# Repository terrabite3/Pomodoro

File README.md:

# Pomodoro

This is a tomato-shaped timer that counts down from 25 minutes.

## Hardware

* ATmega328p or compatible (I used ATmega8 due to supply chain issues)
* USB Micro-B power
* Four-digit 7-segment multiplexed display with colon LEDs
* Reset button
* Wheel potentiometer to adjust brightness
* Extra GPIO is exposed on a header
* Designed to be mostly assembled by JLCPCB

## Software

* Hard-coded 25 minute countdown
* Flashes 00:00 for one minute after countdown finishes
* Full shutdown after count is complete to save power
* Brightness adjustment goes down "off" to reduce visual distraction. At the start of the countdown, the display will start on and fade down to the selected brightness after 10 seconds. The flashing at the end of the countdown ignores the brightness setting.

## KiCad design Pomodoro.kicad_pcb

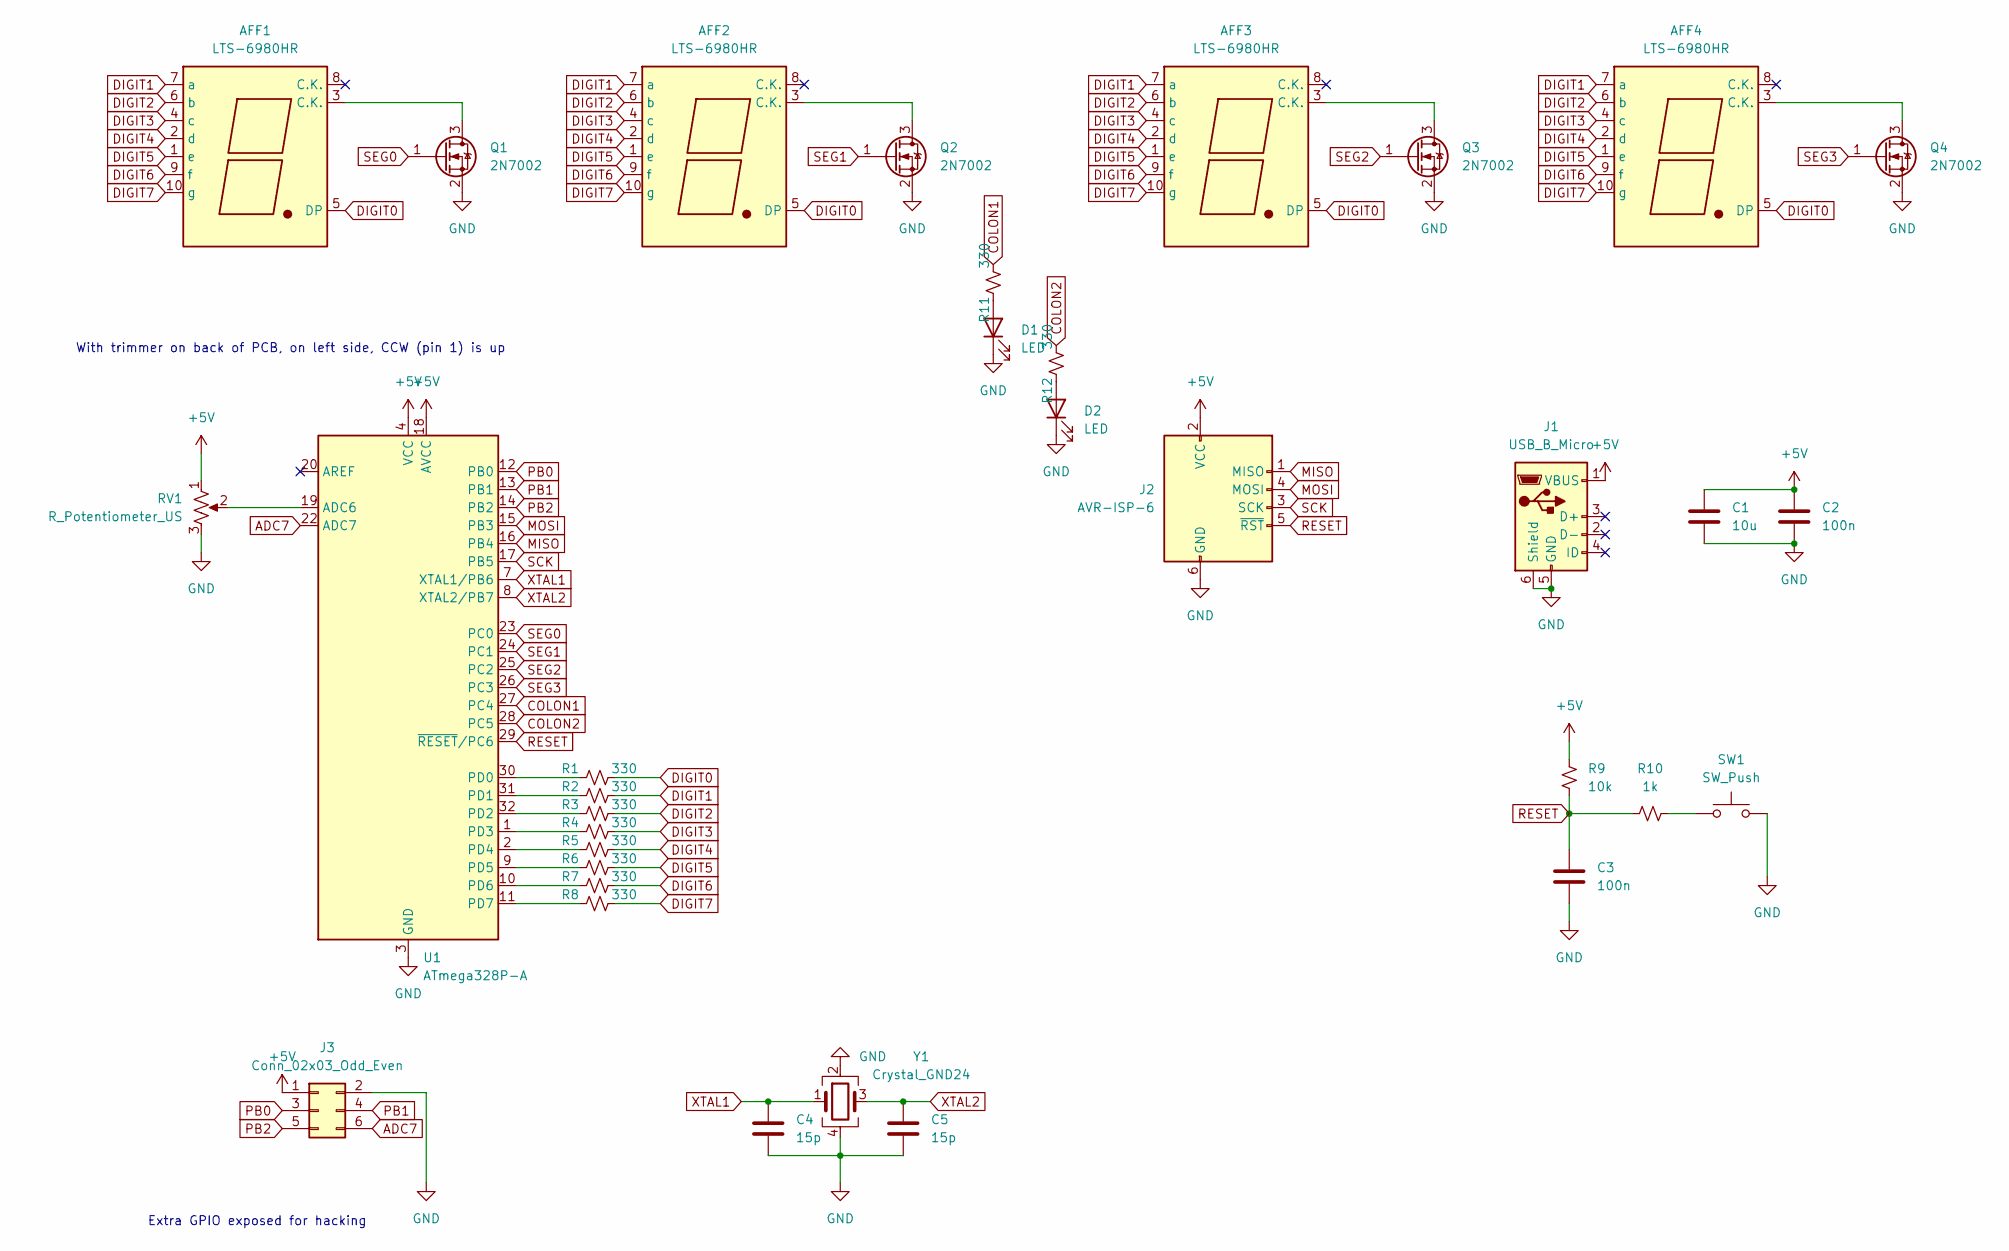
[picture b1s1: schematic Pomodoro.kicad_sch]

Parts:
AFF1, AFF2, AFF3, AFF4: LTS-6980HR; 7SegmentLED_LTS6760_LTS6780
C1: 10u; C_0805_2012Metric
C2, C3: 100n; C_0402_1005Metric
C4, C5: 15p; C_0402_1005Metric
D1, D2: LED; LED_D3.0mm
J1: USB_B_Micro; USB_Micro-B_Amphenol_10118194_Horizontal
J2: AVR-ISP-6; PinHeader_2x03_P2.54mm_Vertical_SMD
J3: Conn_02x03_Odd_Even; PinHeader_2x03_P2.54mm_Vertical_SMD
Q1, Q2, Q3, Q4: 2N7002; SOT-23
R1, R2, R3, R4, R5, R6, R7, R8, R11, R12: 330; R_0402_1005Metric
R9: 10k; R_0402_1005Metric
R10: 1k; R_0402_1005Metric
RV1: R_Potentiometer_US; Potentiometer_Bourns_3352T
SW1: SW_Push; SW_PUSH_6mm
U1: ATmega328P-A; TQFP-32_7x7mm_P0.8mm
Y1: Crystal_GND24; Crystal_SMD_3225-4Pin_3.2x2.5mm

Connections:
+5V: C1.1, C2.1, J1.1 (VBUS), J2.2 (VCC), J3.1, R9.2, RV1.1, U1.4 (VCC), U1.6 (VCC), U1.18 (AVCC)
ADC7: J3.6, U1.22 (ADC7)
COLON1: R11.2, U1.27 (PC4)
COLON2: R12.2, U1.28 (PC5)
DIGIT0: AFF1.5 (DP), AFF2.5 (DP), AFF3.5 (DP), AFF4.5 (DP), R1.2
DIGIT1: AFF1.7 (a), AFF2.7 (a), AFF3.7 (a), AFF4.7 (a), R2.2
DIGIT2: AFF1.6 (b), AFF2.6 (b), AFF3.6 (b), AFF4.6 (b), R3.2
DIGIT3: AFF1.4 (c), AFF2.4 (c), AFF3.4 (c), AFF4.4 (c), R4.2
DIGIT4: AFF1.2 (d), AFF2.2 (d), AFF3.2 (d), AFF4.2 (d), R5.2
DIGIT5: AFF1.1 (e), AFF2.1 (e), AFF3.1 (e), AFF4.1 (e), R6.2
DIGIT6: AFF1.9 (f), AFF2.9 (f), AFF3.9 (f), AFF4.9 (f), R7.2
DIGIT7: AFF1.10 (g), AFF2.10 (g), AFF3.10 (g), AFF4.10 (g), R8.2
GND: C1.2, C2.2, C3.2, C4.2, C5.2, D1.1 (K), D2.1 (K), J1.5 (GND), J1.6 (Shield), J2.6 (GND), J3.2, Q1.2 (S), Q2.2 (S), Q3.2 (S), Q4.2 (S), RV1.3, SW1.2, U1.3 (GND), U1.5 (GND), U1.21 (GND), Y1.2, Y1.4
MISO: J2.1 (MISO), U1.16 (PB4)
MOSI: J2.4 (MOSI), U1.15 (PB3)
unnamed: AFF1.3 (C.K.), Q1.3 (D)
unnamed: AFF2.3 (C.K.), Q2.3 (D)
unnamed: AFF3.3 (C.K.), Q3.3 (D)
unnamed: AFF4.3 (C.K.), Q4.3 (D)
unnamed: D1.2 (A), R11.1
unnamed: D2.2 (A), R12.1
unnamed: R10.2, SW1.1
unnamed: R4.1, U1.1 (PD3)
unnamed: R5.1, U1.2 (PD4)
unnamed: R6.1, U1.9 (PD5)
unnamed: R7.1, U1.10 (PD6)
unnamed: R8.1, U1.11 (PD7)
unnamed: RV1.2, U1.19 (ADC6)
unnamed: R1.1, U1.30 (PD0)
unnamed: R2.1, U1.31 (PD1)
unnamed: R3.1, U1.32 (PD2)
PB0: J3.3, U1.12 (PB0)
PB1: J3.4, U1.13 (PB1)
PB2: J3.5, U1.14 (PB2)
RESET: C3.1, J2.5 (~RST), R9.1, R10.1, U1.29 (~RESET/PC6)
SCK: J2.3 (SCK), U1.17 (PB5)
SEG0: Q1.1 (G), U1.23 (PC0)
SEG1: Q2.1 (G), U1.24 (PC1)
SEG2: Q3.1 (G), U1.25 (PC2)
SEG3: Q4.1 (G), U1.26 (PC3)
XTAL1: C4.1, U1.7 (XTAL1/PB6), Y1.1
XTAL2: C5.1, U1.8 (XTAL2/PB7), Y1.3

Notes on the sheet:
Extra GPIO exposed for hacking
With trimmer on back of PCB, on left side, CCW (pin 1) is up

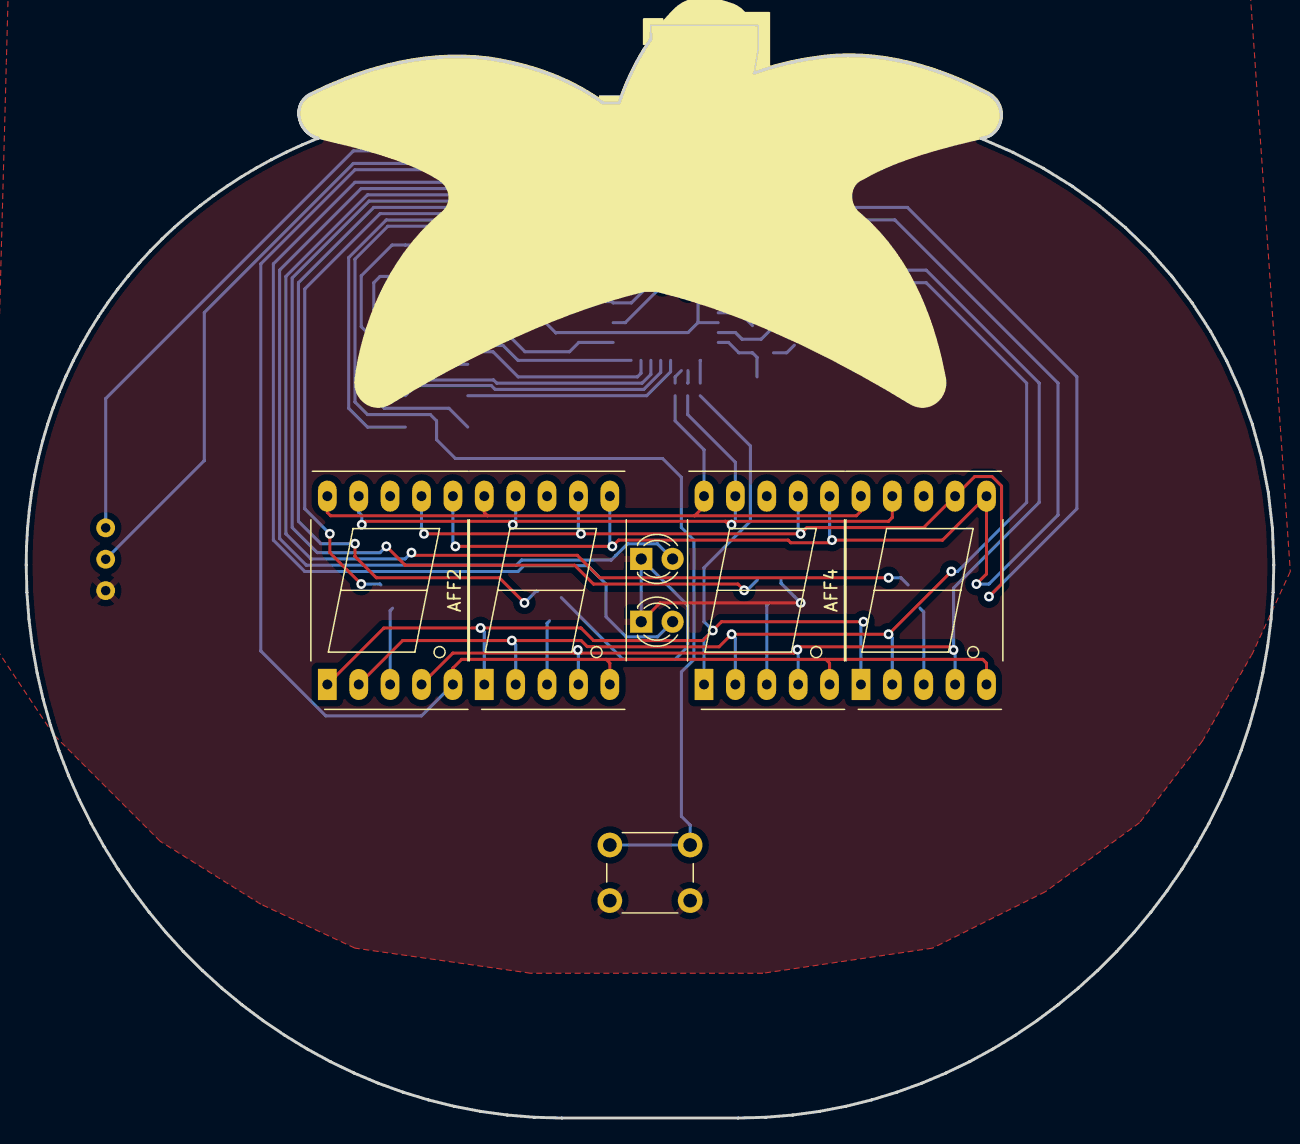
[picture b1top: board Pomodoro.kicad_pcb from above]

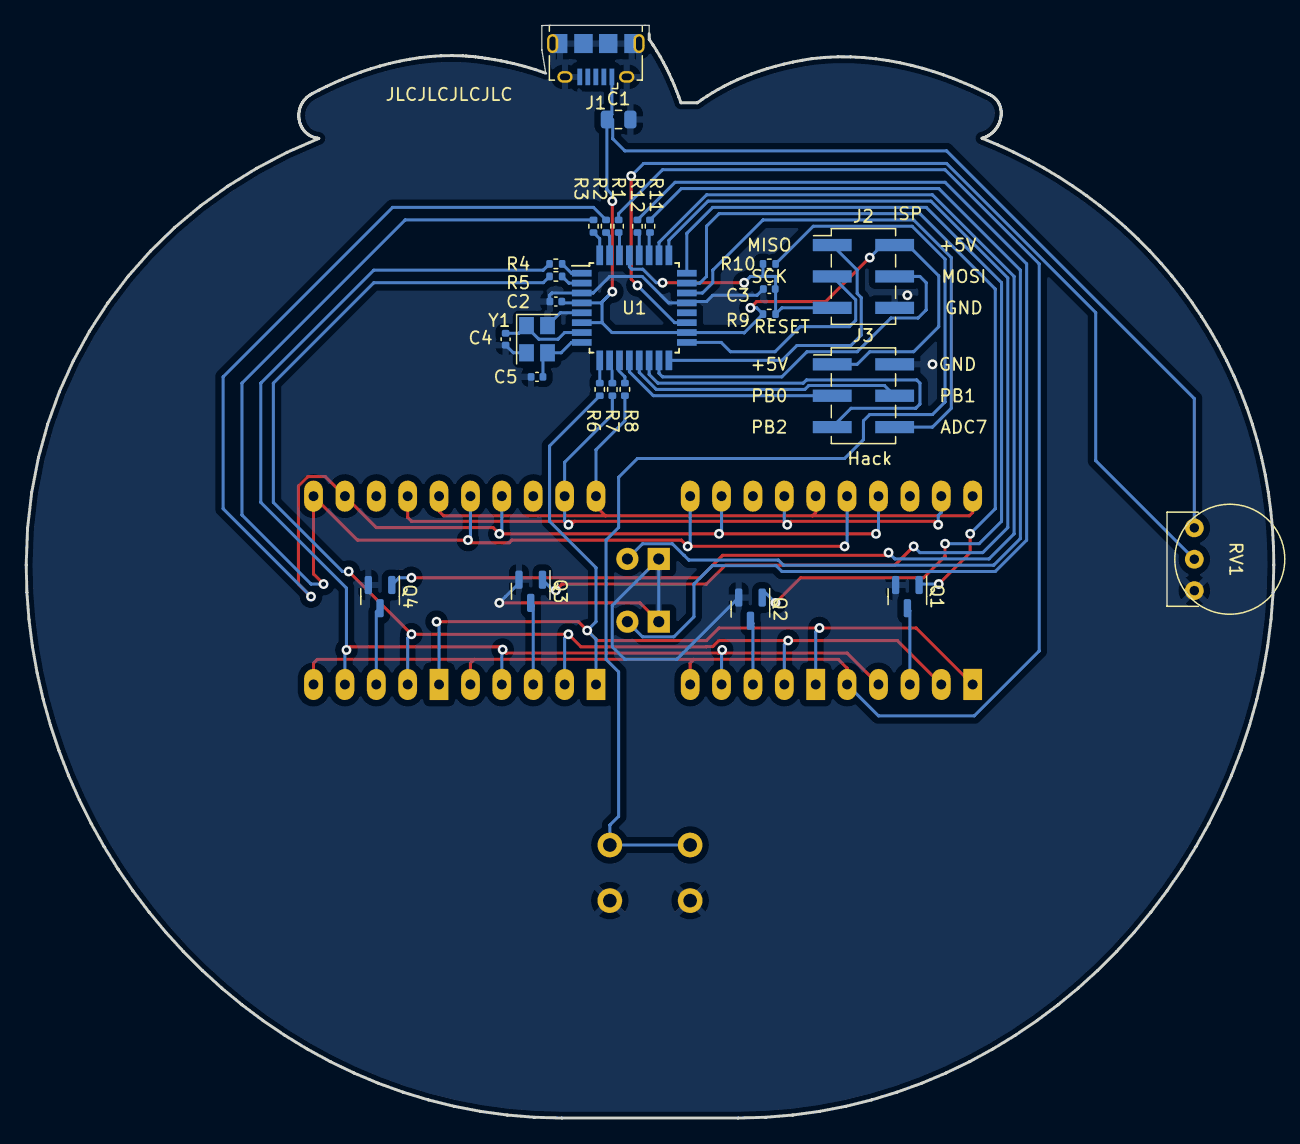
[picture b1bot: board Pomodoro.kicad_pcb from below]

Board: 2 copper layers, 101.0 x 88.4 mm, 34 parts (27 on the bottom side), 42 nets.

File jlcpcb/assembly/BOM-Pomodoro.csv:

Comment,Designator,Footprint,LCSC
1k,R10,R_0402_1005Metric,C11702
USB_B_Micro,J1,USB_Micro-B_Amphenol_10118194_Horizontal,C132563
100n,"C2,C3",C_0402_1005Metric,C1525
15p,"C4,C5",C_0402_1005Metric,C1548
10u,C1,C_0805_2012Metric,C15850
330,"R1,R11,R12,R2,R3,R4,R5,R6,R7,R8",R_0402_1005Metric,C25104
10k,R9,R_0402_1005Metric,C25744
2N7002,"Q1,Q2,Q3,Q4",SOT-23,C8545
Crystal_GND24,Y1,Crystal_SMD_3225-4Pin_3.2x2.5mm,C9002

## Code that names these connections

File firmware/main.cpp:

#include <avr/io.h>
#include <avr/interrupt.h>
#include <avr/sleep.h>

#include <util/delay_basic.h>

/* Pin map

PB0     hack header
PB1     hack header
PB2     hack header
PB3     MOSI (JTAG header)
PB4     MISO (JTAG header)
PB5     SCK (JTAG header)
PB6     XTAL
PB7     XTAL

PC0     SEG0
PC1     SEG1
PC2     SEG2
PC3     SEG3
PC4     COLON1
PC5     COLON2
PC6     RESET (button)

PD0     DIGIT0
...     ...
PD7     DIGIT7

ADC6    pot
ADC7    hack header

*/

#define RESET_TIME 25 * 60

volatile int16_t countdown = RESET_TIME;

ISR(TIMER1_COMPA_vect)
{
    countdown--;
}

void setupTimer()
{
    // setup the timer to fire every 1 second
    
    // Timer count calculated with https://eleccelerator.com/avr-timer-calculator/
    // 12 MHz, 16-bit, Prescaler = Clk/256, Real Time = 1 second
    TCCR1A = 0;         // Nothing needed here
    TCCR1B =  1<<WGM12  // CTC mode (clear timer on compare match)
            | 1<<CS12;  // Clk/256 prescaler
    OCR1A = 46875;

    TIMSK = 1<<OCIE1A;  // Enable the interrupt for output compare A match

    sei(); // Enable global interrupt flag
}

uint8_t digitCode0 = 0;
uint8_t digitCode1 = 0;
uint8_t digitCode2 = 0;
uint8_t digitCode3 = 0;

void noDigit()
{
    PORTC = 0;
}

void nextDigit()
{
    static uint8_t digit = 0;

    digit = (digit + 1) % 4;

    // Reset segment drivers
    PORTC &= ~(1<<PC0 | 1<<PC1 | 1<<PC2 | 1<<PC3);

    switch (digit)
    {
    case 0:
        PORTC |= 1<<PC0;
        PORTD = digitCode0;
        break;
    case 1:
        PORTC |= 1<<PC1;
        PORTD = digitCode1;
        break;
    case 2:
        PORTC |= 1<<PC2;
        PORTD = digitCode2;
        break;
    case 3:
        PORTC |= 1<<PC3;
        PORTD = digitCode3;
        break;
    }
}

uint8_t numberToCode(uint8_t number)
{
    switch (number)
    {
    case 0:
        return 0b01111110;
    case 1:
        return 0b00001100;
    case 2:
        return 0b10110110;
    case 3:
        return 0b10011110;
    case 4:
        return 0b11001100;
    case 5:
        return 0b11011010;
    case 6:
        return 0b11111010;
    case 7:
        return 0b00001110;
    case 8:
        return 0b11111110;
    case 9:
        return 0b11011110;
    case 10: // All off
        return 0b00000000;
    default: // Light decimal point to indicate error
        return 0b00000001;
    }
}

void updateDigits()
{
    // Normal behavior
    if (countdown >= 0)
    {
        uint8_t minutes = countdown / 60;
        uint8_t minutesOnes = minutes % 10;
        uint8_t minutesTens = minutes / 10;

        uint8_t seconds = countdown % 60;
        uint8_t secondsOnes = seconds % 10;
        uint8_t secondsTens = seconds / 10;

        digitCode0 = numberToCode(minutesTens);
        digitCode1 = numberToCode(minutesOnes);
        digitCode2 = numberToCode(secondsTens);
        digitCode3 = numberToCode(secondsOnes);
    }
    // Countdown has underflowed, less than a minute ago
    // Blink 00:00
    else if (countdown >= -60) 
    {
        if (countdown % 2)
        {
            digitCode0 = numberToCode(10);
            digitCode1 = numberToCode(10);
            digitCode2 = numberToCode(10);
            digitCode3 = numberToCode(10);
        }
        else
        {
            digitCode0 = numberToCode(0);
            digitCode1 = numberToCode(0);
            digitCode2 = numberToCode(0);
            digitCode3 = numberToCode(0);
        }
    }
    else
    {
        // Go into low power mode until the reset button is pressed
        cli(); // Disable interrupts

        // Turn off all LEDs and set pins as inputs
        PORTC = 0;
        PORTD = 0;
        DDRC = 0;
        DDRD = 0;

        set_sleep_mode(SLEEP_MODE_PWR_DOWN);
        sleep_mode();
    }
}

int main(void)
{
    setupTimer();

    // AVCC reference, ADC6
    ADMUX = 1<<REFS0 | 6;
    // Enable the ADC, and set it to maximum clock division. We don't need it to be fast.
    ADCSRA = 1<<ADEN | 7;


    DDRC |= 1<<PC0 | 1<<PC1 | 1<<PC2 | 1<<PC3 | 1<<PC4 | 1<<PC5;
    DDRD = 0xFF;

    uint16_t adcValue = 1023;
    while (1)
    {
        // If there isn't currently an ADC conversion, read the value and start a new conversion
        if (!(ADCSRA & (1<<ADSC)))
        {
            adcValue = ADC;
            ADCSRA |= 1<<ADSC;
        }

        updateDigits();

        // If the brightness is turned down, turn it on for the first 10 seconds anyways,
        // dimming over 10 seconds
        if (countdown > RESET_TIME - 10)
        {
            int16_t secondsElapsed = RESET_TIME - countdown;
            int16_t minBrightness = 1023 - 100 * secondsElapsed;
            if (adcValue < minBrightness)
                adcValue = minBrightness;
        }
        // Blink anyways when the countdown ends
        else if (countdown <= 0)
        {
            adcValue = 1023;
        }

        if (adcValue == 0)
        {
            noDigit();
            _delay_loop_2(1024);
        }
        else if (adcValue >= 1023)
        {
            nextDigit();
            _delay_loop_2(1024);
        }
        else
        {
            nextDigit();
            // Keep the digit on for a time determined by the ADC
            _delay_loop_2(adcValue);

            noDigit();
            // Turn off for the inverse
            _delay_loop_2(1024 - adcValue - 1);
        }

    }
}

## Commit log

2022-02-12 Upload files
2022-02-12 Change countdown to 25 minutes
